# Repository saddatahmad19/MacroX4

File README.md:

# MacroX4
## by Saddat Ahmad
### Started January 3rd, 2024 | 2:31 AM CST

## Introduction
Hello, my name is Saddat Ahmad, and without further introduction, I present the MacroX4. An open source, wireless macropad with 18 keys, 2 rotary encoder switches, and 2 RGB lights.

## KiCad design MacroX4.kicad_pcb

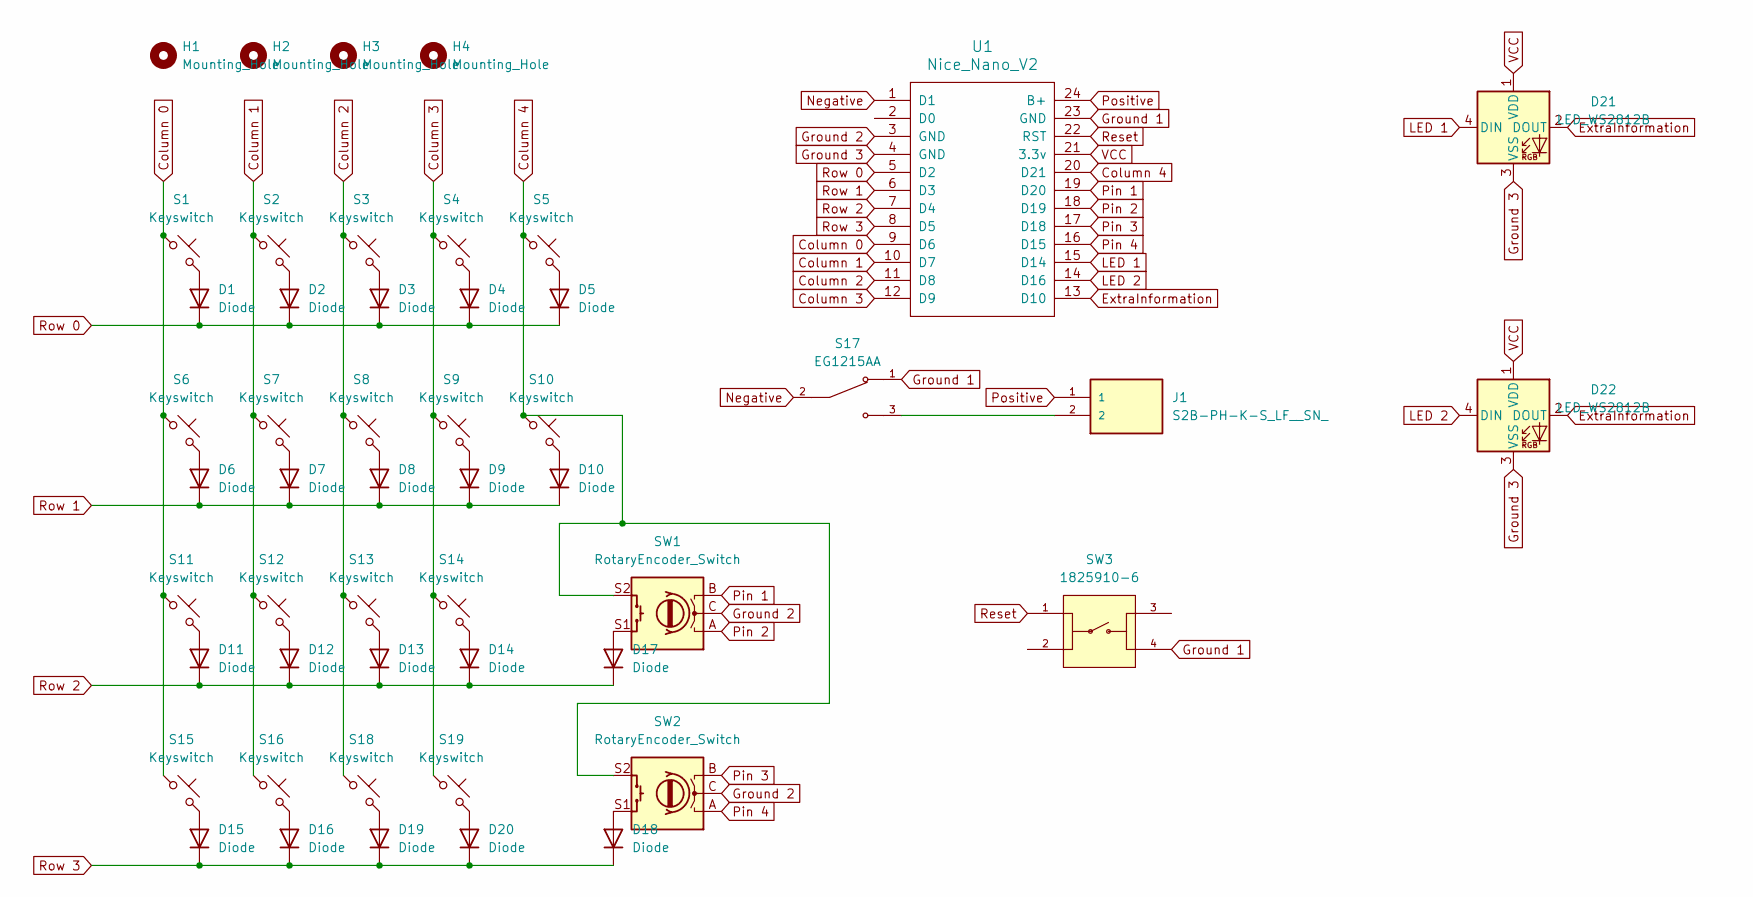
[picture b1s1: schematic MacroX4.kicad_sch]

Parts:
D1, D2, D3, D4, D5, D6, D7, D8, D9, D10, D11, D12, D13, D14, D15, D16, D17, D18, D19, D20: Diode; Diode_SOD-123
D21, D22: LED_WS2812B
H1, H2, H3, H4: Mounting_Hole; MountingHole_2.5mm
J1: S2B-PH-K-S_LF__SN_; JST_S2B-PH-K-S_LF__SN_
S1, S2, S3, S4, S5, S6, S7, S8, S9, S10, S11, S12, S13, S14, S15, S16, S18, S19: Keyswitch; Hotswap_MX_1.00u
S17: EG1215AA; SW_EG1215AA; PARTREV A
SW1, SW2: RotaryEncoder_Switch; RotaryEncoder_Alps_EC11E-Switch_Vertical_H20mm
SW3: 1825910-6; SW_1825910-6-4; PARTREV C10
U1: Nice_Nano_V2

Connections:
Column 0: S1.1, S6.1, S11.1, S15.1, U1.9 (D6)
Column 1: S2.1, S7.1, S12.1, S16.1, U1.10 (D7)
Column 2: S3.1, S8.1, S13.1, S18.1, U1.11 (D8)
Column 3: S4.1, S9.1, S14.1, S19.1, U1.12 (D9)
Column 4: S5.1, S10.1, SW1.S2, SW2.S2, U1.20 (D21)
ExtraInformation: D21.2 (DOUT), D22.2 (DOUT), U1.13 (D10)
Ground 1: S17.1, SW3.4, U1.23 (GND)
Ground 2: SW1.C, SW2.C, U1.3 (GND)
Ground 3: D21.3 (VSS), D22.3 (VSS), U1.4 (GND)
LED 1: D21.4 (DIN), U1.15 (D14)
LED 2: D22.4 (DIN), U1.14 (D16)
Negative: S17.2, U1.1 (D1)
unnamed: D1.2 (A), S1.2
unnamed: D2.2 (A), S2.2
unnamed: D3.2 (A), S3.2
unnamed: D4.2 (A), S4.2
unnamed: D5.2 (A), S5.2
unnamed: D6.2 (A), S6.2
unnamed: D7.2 (A), S7.2
unnamed: D8.2 (A), S8.2
unnamed: D9.2 (A), S9.2
unnamed: D10.2 (A), S10.2
unnamed: D11.2 (A), S11.2
unnamed: D12.2 (A), S12.2
unnamed: D13.2 (A), S13.2
unnamed: D14.2 (A), S14.2
unnamed: D15.2 (A), S15.2
unnamed: D16.2 (A), S16.2
unnamed: D17.2 (A), SW1.S1
unnamed: D18.2 (A), SW2.S1
unnamed: D19.2 (A), S18.2
unnamed: D20.2 (A), S19.2
unnamed: J1.2, S17.3
Pin 1: SW1.B, U1.19 (D20)
Pin 2: SW1.A, U1.18 (D19)
Pin 3: SW2.B, U1.17 (D18)
Pin 4: SW2.A, U1.16 (D15)
Positive: J1.1, U1.24 (B+)
Reset: SW3.1, U1.22 (RST)
Row 0: D1.1 (K), D2.1 (K), D3.1 (K), D4.1 (K), D5.1 (K), U1.5 (D2)
Row 1: D6.1 (K), D7.1 (K), D8.1 (K), D9.1 (K), D10.1 (K), U1.6 (D3)
Row 2: D11.1 (K), D12.1 (K), D13.1 (K), D14.1 (K), D17.1 (K), U1.7 (D4)
Row 3: D15.1 (K), D16.1 (K), D18.1 (K), D19.1 (K), D20.1 (K), U1.8 (D5)
VCC: D21.1 (VDD), D22.1 (VDD), U1.21 (3.3v)

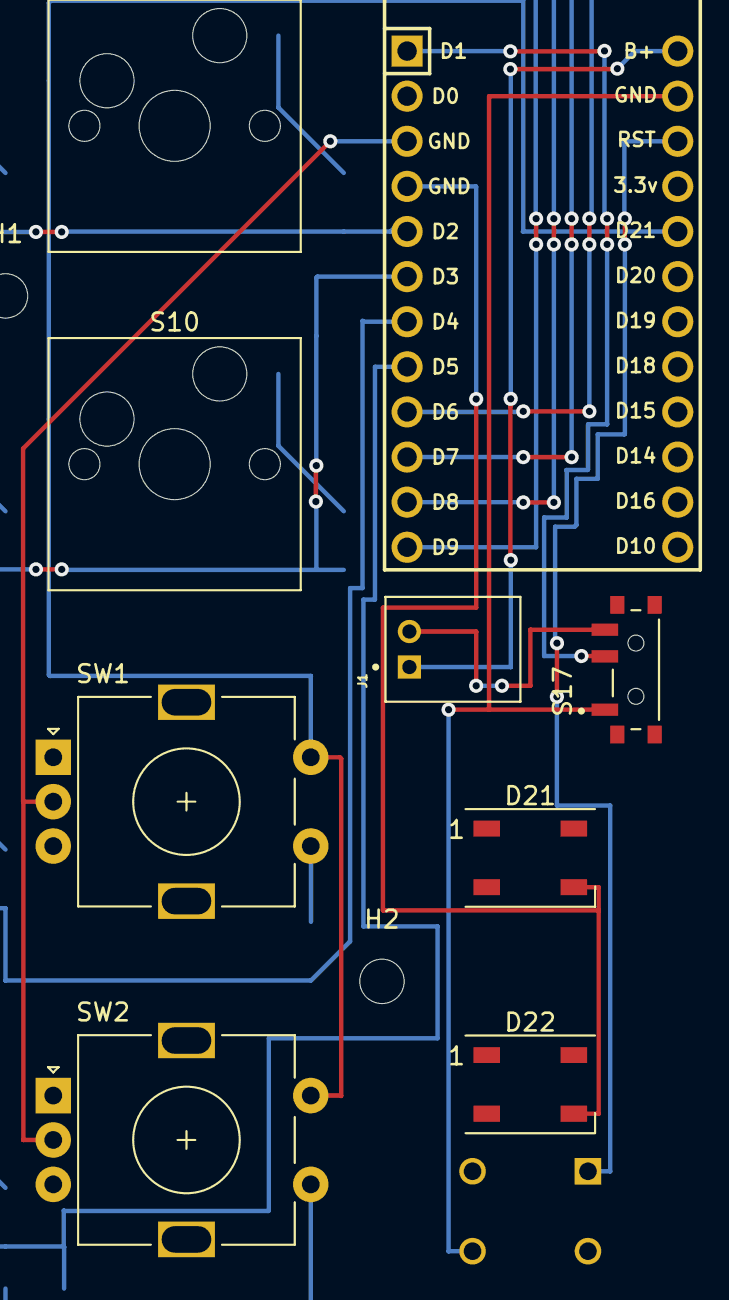
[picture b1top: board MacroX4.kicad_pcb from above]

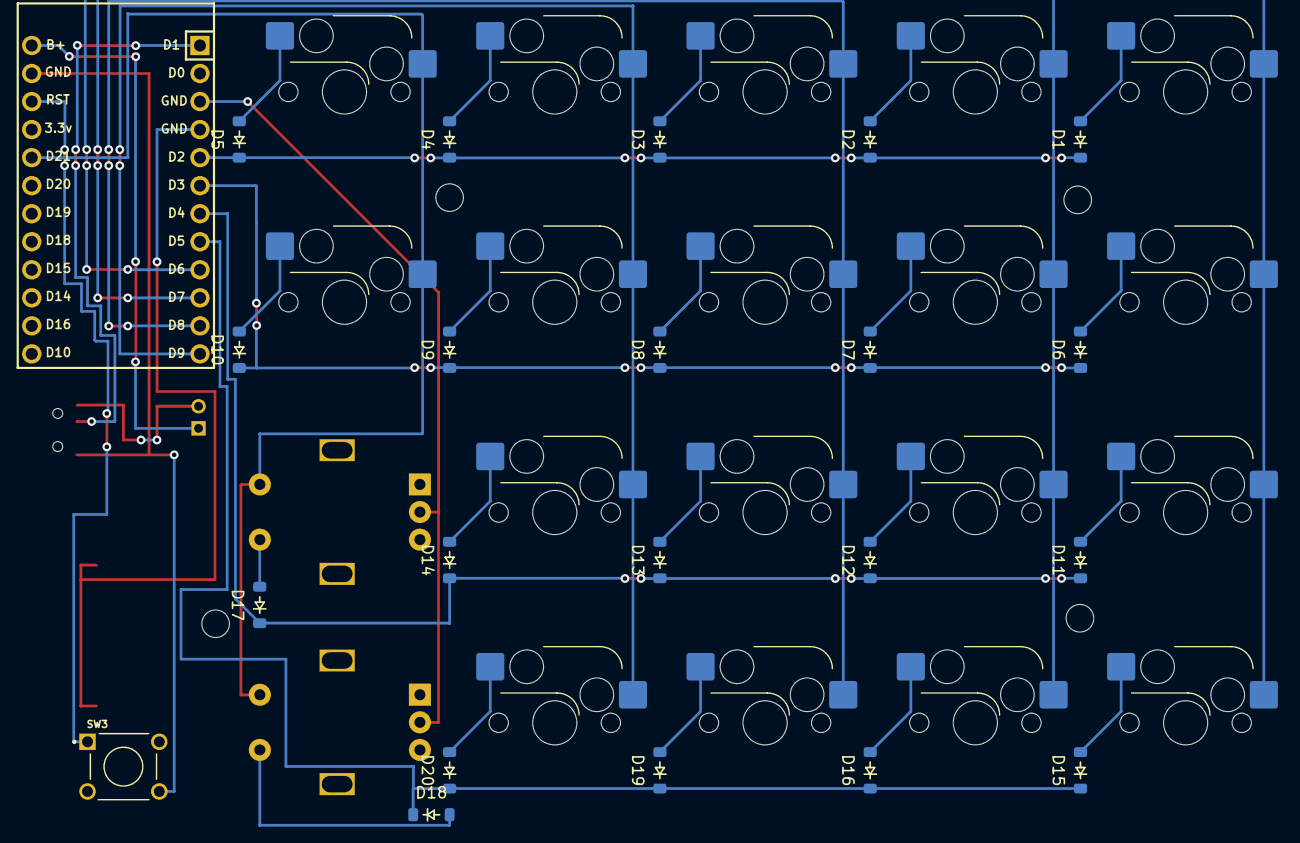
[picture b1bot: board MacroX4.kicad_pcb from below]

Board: 2 copper layers, 50 parts (21 on the bottom side), 44 nets.

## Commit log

2024-01-03 Wiring and more components
